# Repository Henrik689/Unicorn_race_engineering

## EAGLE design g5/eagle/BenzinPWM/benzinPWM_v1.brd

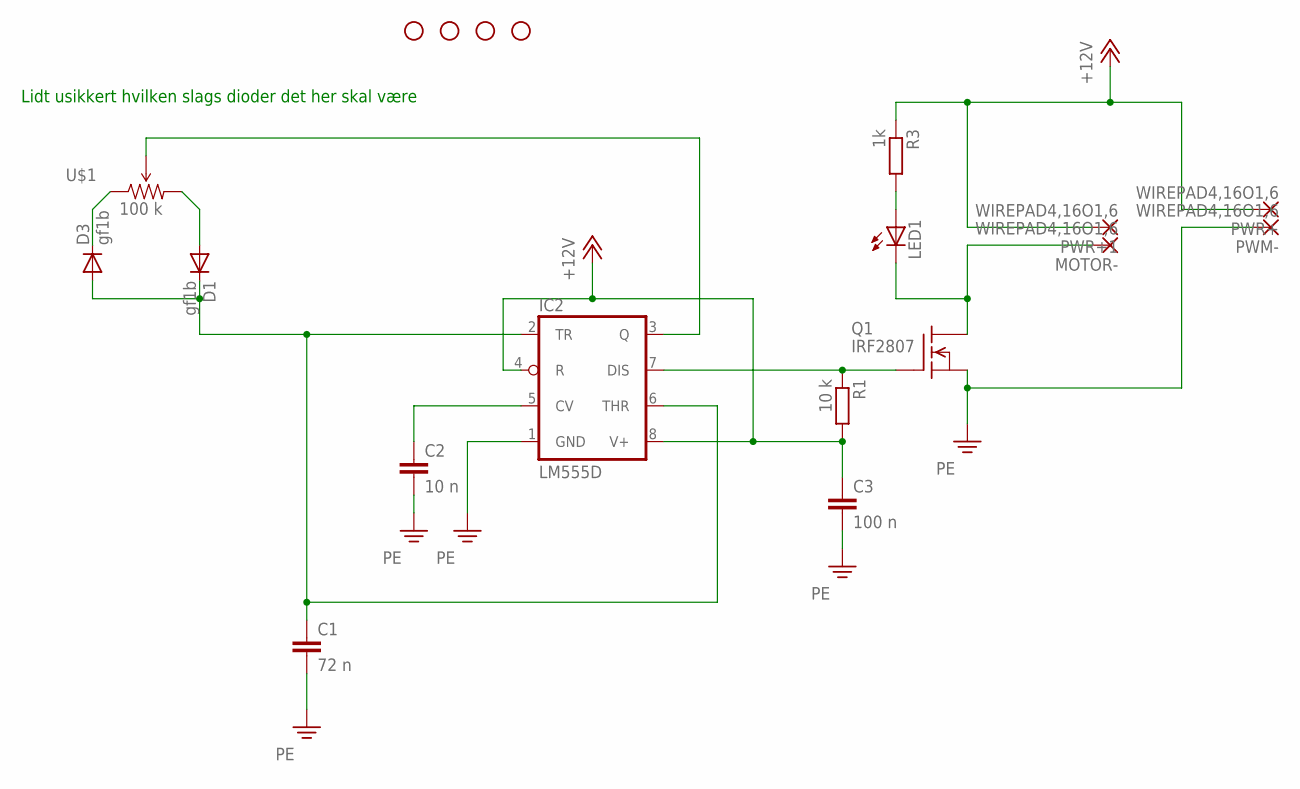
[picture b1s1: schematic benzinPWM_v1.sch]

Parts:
C1: 72 n; C0805
C2: 10 n; C0805
C3: 100 n; C0805
D1, D3: gf1b; GF1
IC2: LM555D; SO08
JP3, JP4, JP5, JP6: STAND-OFF
LED1: LEDCHIPLED_0805; CHIPLED_0805
MOTOR-: WIREPAD4,16O1,6; 4,16O1,6
PWM-: WIREPAD4,16O1,6; 4,16O1,6
PWR+, PWR+1: WIREPAD4,16O1,6; 4,16O1,6
Q1: IRF2807; TO220
R1: 10 k; M0805
R3: 1k; M0805
U$1: 100 k; 3362U-2

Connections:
+12V: C3.1, IC2.4 (R), IC2.8 (V+), PWR+.1, PWR+1.1, R1.2, R3.1
unnamed: C1.1, D1.C, D3.A, IC2.2 (TR), IC2.6 (THR)
unnamed: D1.A, U$1.3 (CW)
unnamed: D3.C, U$1.1 (CCW)
unnamed: C2.1, IC2.5 (CV)
unnamed: IC2.7 (DIS), Q1.1 (G), R1.1
unnamed: LED1.A, R3.2
unnamed: IC2.3 (Q), U$1.2 (WIPER)
unnamed: LED1.C, MOTOR-.1, Q1.2 (D)
PE: C1.2, C2.2, C3.2, IC2.1 (GND), PWM-.1, Q1.3 (S)

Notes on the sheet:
Lidt usikkert hvilken slags dioder det her skal være

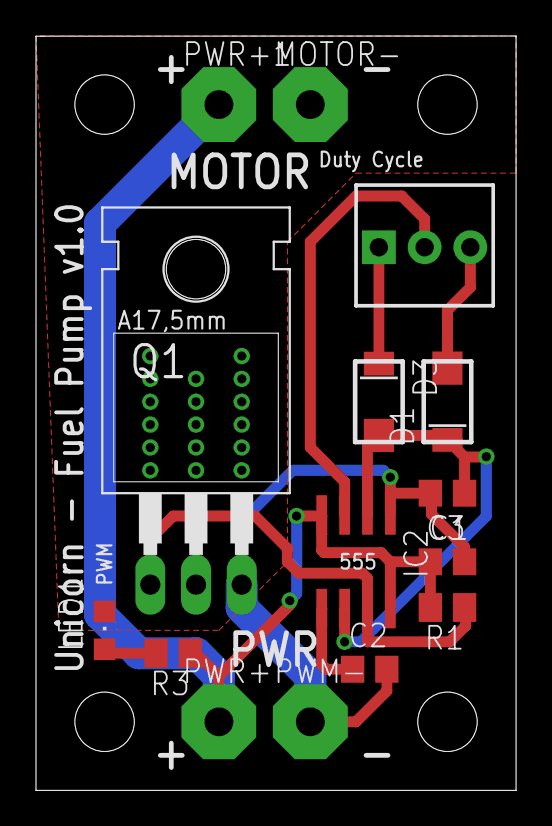
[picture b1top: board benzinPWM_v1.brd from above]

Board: 2 copper layers, 26.7 x 41.9 mm, 19 parts (0 on the bottom side), 10 nets.
